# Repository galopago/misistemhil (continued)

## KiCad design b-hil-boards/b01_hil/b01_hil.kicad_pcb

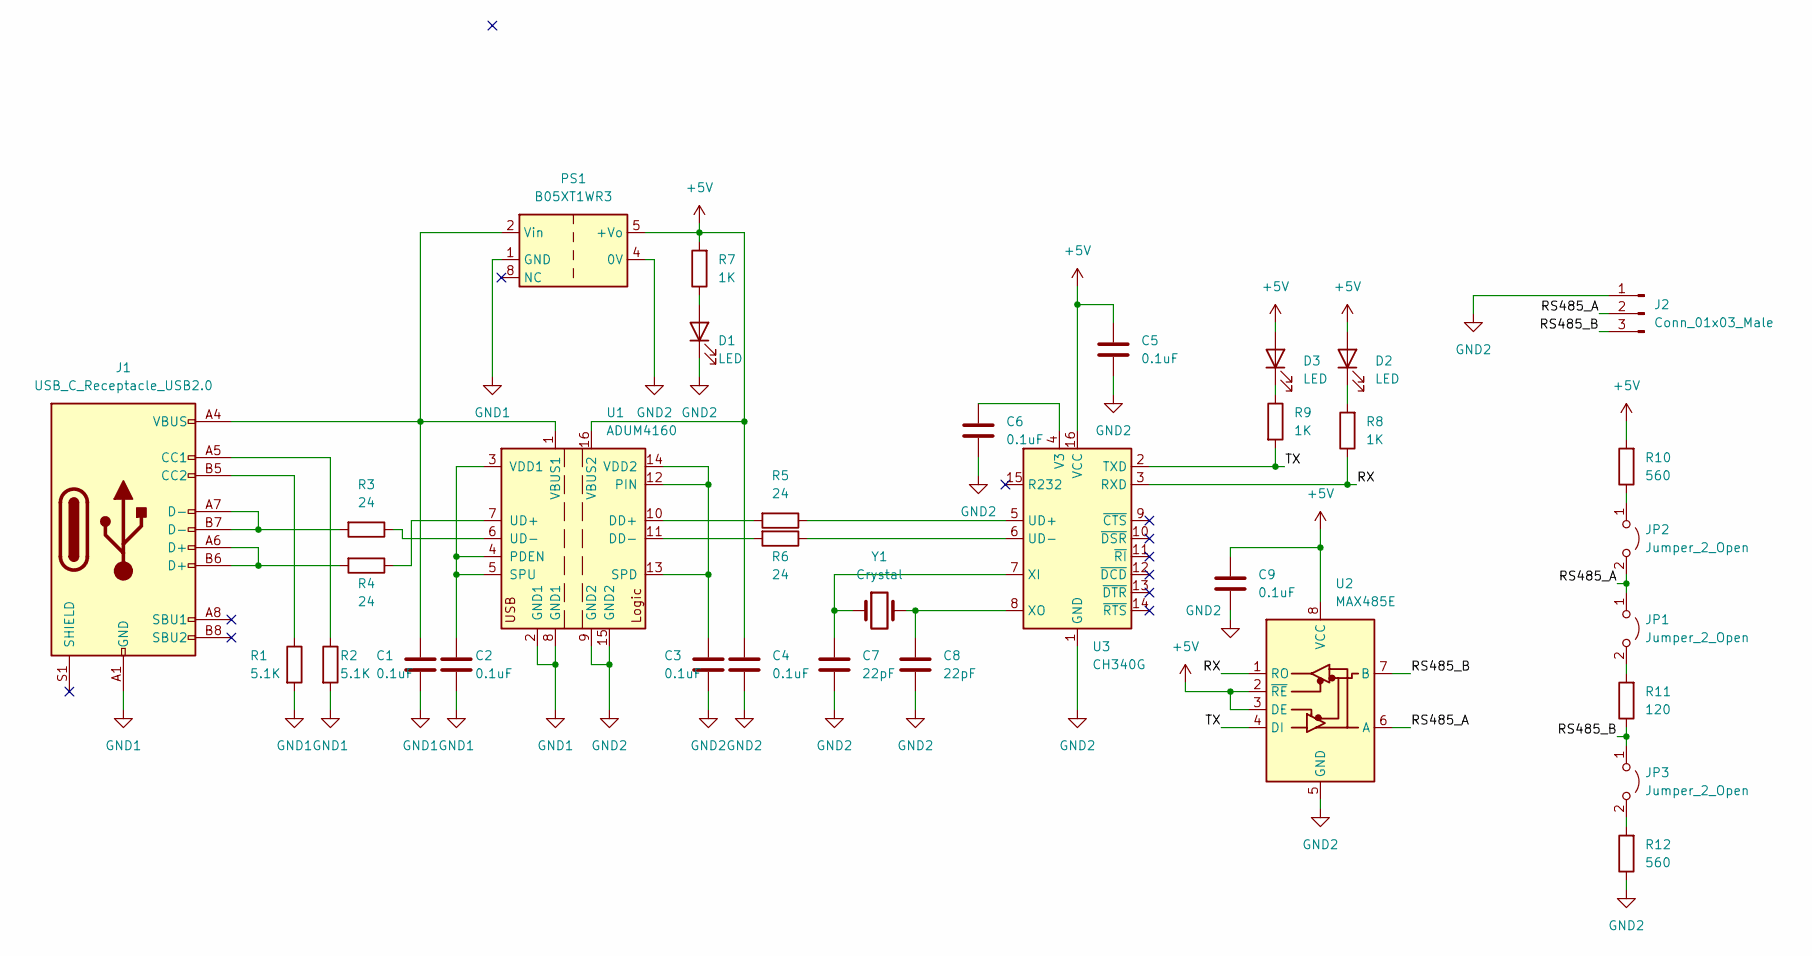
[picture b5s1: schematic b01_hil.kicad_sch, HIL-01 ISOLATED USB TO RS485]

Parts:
C1, C2, C3, C4, C5, C6, C9: 0.1uF; C_0805_2012Metric_Pad1.18x1.45mm_HandSolder
C7, C8: 22pF; C_0805_2012Metric_Pad1.18x1.45mm_HandSolder
D1, D2, D3: LED; D_0805_2012Metric_Pad1.15x1.40mm_HandSolder
J1: USB_C_Receptacle_USB2.0; USB_C_Receptacle_HRO_TYPE-C-31-M-12
J2: Conn_01x03_Male; TerminalBlock_4Ucon_1x03_P3.50mm_Horizontal
JP1, JP2, JP3: Jumper_2_Open; PinHeader_1x02_P2.54mm_Vertical
PS1: B05XT1WR3; Converter_DCDC_Mornsun_B05_XT_1WR3_SMD
R1, R2: 5.1K; R_0805_2012Metric_Pad1.20x1.40mm_HandSolder
R3, R4, R5, R6: 24; R_0805_2012Metric_Pad1.20x1.40mm_HandSolder
R7, R8, R9: 1K; R_0805_2012Metric_Pad1.20x1.40mm_HandSolder
R10, R12: 560; R_0805_2012Metric_Pad1.20x1.40mm_HandSolder
R11: 120; R_0805_2012Metric_Pad1.20x1.40mm_HandSolder
U1: ADUM4160; SOIC-16W_7.5x10.3mm_P1.27mm
U2: MAX485E; SOP-8_3.9x4.9mm_P1.27mm
U3: CH340G; SOIC-16_3.9x9.9mm_P1.27mm
Y1: Crystal; Crystal_SMD_HC49-SD_HandSoldering_Compact

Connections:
+5V: C4.1, C5.1, C9.1, D2.2 (A), D3.2 (A), PS1.5 (+Vo), R7.2, R10.2, U1.16 (VBUS2), U2.2 (~RE), U2.3 (DE), U2.8 (VCC), U3.16 (VCC)
/RS485_A: J2.2, JP1.1 (A), JP2.2 (B), U2.6 (A)
/RS485_B: J2.3, JP3.1 (A), R11.1, U2.7 (B)
/RX: R8.1, U2.1 (RO), U3.3 (RXD)
/TX: R9.2, U2.4 (DI), U3.2 (TXD)
GND1: C1.2, C2.2, J1.A1 (GND), J1.A12 (GND), J1.B1 (GND), J1.B12 (GND), PS1.1 (GND), R1.2, R2.2, U1.2 (GND1), U1.8 (GND1)
GND2: C3.2, C4.2, C5.2, C6.2, C7.2, C8.2, C9.2, D1.1 (K), J2.1, PS1.4 (0V), R12.1, U1.9 (GND2), U1.15 (GND2), U2.5 (GND), U3.1 (GND)
unnamed: C1.1, J1.A4 (VBUS), J1.A9 (VBUS), J1.B4 (VBUS), J1.B9 (VBUS), PS1.2 (Vin), U1.1 (VBUS1)
unnamed: C2.1, U1.3 (VDD1), U1.4 (PDEN), U1.5 (SPU)
unnamed: C3.1, U1.12 (PIN), U1.13 (SPD), U1.14 (VDD2)
unnamed: C6.1, U3.4 (V3)
unnamed: C7.1, U3.7 (XI), Y1.1
unnamed: C8.1, U3.8 (XO), Y1.2
unnamed: D1.2 (A), R7.1
unnamed: D2.1 (K), R8.2
unnamed: D3.1 (K), R9.1
unnamed: J1.A5 (CC1), R2.1
unnamed: J1.A6 (D+), J1.B6 (D+), R4.2
unnamed: J1.A7 (D-), J1.B7 (D-), R3.2
unnamed: J1.B5 (CC2), R1.1
unnamed: JP1.2 (B), R11.2
unnamed: JP2.1 (A), R10.1
unnamed: JP3.2 (B), R12.2
unnamed: R3.1, U1.6 (UD-)
unnamed: R4.1, U1.7 (UD+)
unnamed: R5.1, U3.5 (UD+)
unnamed: R5.2, U1.10 (DD+)
unnamed: R6.1, U3.6 (UD-)
unnamed: R6.2, U1.11 (DD-)

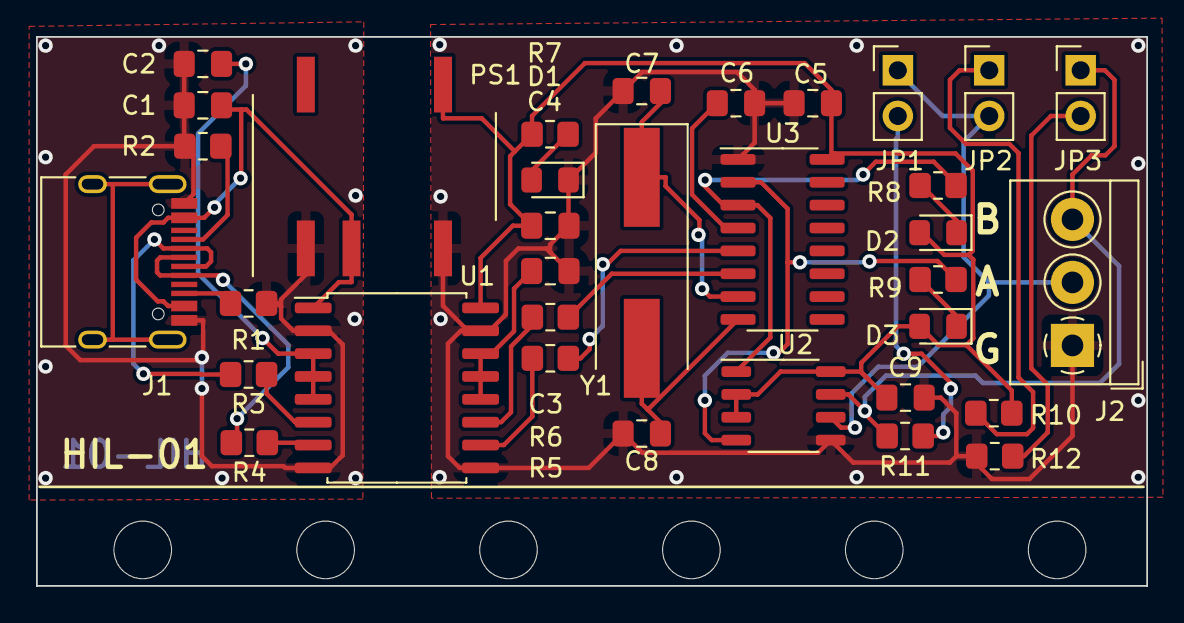
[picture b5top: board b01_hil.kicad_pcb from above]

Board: 2 copper layers, 61.7 x 30.5 mm, 34 parts (0 on the bottom side), 29 nets.

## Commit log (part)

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2024-02-11 hil logo
2024-02-11 started readme
2024-02-11 started readme+
2024-02-11 template readme trimmed
2024-02-13 started 6.35 screw barrier connector footprint
2024-02-19 updated rs485 footprint
2024-02-19 started hil-00 board
2024-02-25 all traces routed
2024-02-25 improved vias on ground planes
2024-02-25 improved vias on ground planes+
2024-02-25 single gerbers
2024-02-25 panel gerbers
2024-02-25 deleted unused files
2024-02-26 panel gerber
2024-08-05 started a00-backplate first test
2024-08-15 started label panels
2024-08-16 fixed name number
2024-10-27 Changed jumper distances to be compatible with 2.54 pin headers
2026-02-18 Start b02 HIL board card
    - Add b02_hil board: schematic, PCB, project and library files
    - Add b02 assets (datasheets, pinout, images) and gerber exports
    - Update b01_hil project files and add b01 backup archives
2026-02-23 B02 card: routing and silkscreen completed
    - PCB layout and silkscreen finished for b02_hil
2026-02-23 B02 card: add gerbers for panelized board
    - Generate panel gerber and drill files in gerber/panel/
2026-02-25 B03: place all board elements (PCB and schematic)
    - Complete component placement for B03 HIL board
    - Add KiCad project, schematic and PCB layout
    - Include symbol/footprint lib tables and fp-info-cache
    - Add project libraries and assets (ESP32-C3, datasheets)
2026-02-25 B03: route all board traces
    - Complete trace routing for B03 HIL board
    - Update PCB layout (b03.kicad_pcb) and schematic (b03.kicad_sch)
    - Add routing session/export files and backups
2026-02-26 B04: complete trace routing for HIL board
    - Add B04 HIL board project with full PCB routing (b04.kicad_pcb, b04.kicad_sch)
    - Include KiCad project, libraries and assets (ESP32-C3, datasheets)
    - Add B03 Gerber panel output (gerber/panel/) for multi-board fabrication
    - Update backups
2026-02-26 B04: add Gerber output for single board
    - Create Gerber files for single-board fabrication (gerber/single/)
    - Include copper, mask, paste, silkscreen, edge cuts and drill files (PTH/NPTH)
    - Add b04-single.zip package for manufacturer
2026-02-26 B04: add Gerber output for panel
    - Create Gerber files for panel fabrication (gerber/panel/)
    - Include copper, mask, paste, silkscreen, edge cuts and drill files
    - Add b04-panel.zip package for multi-board manufacturer
2026-03-19 chore: refresh KiCad backup archives (b02, b03, b04)
    Remove superseded zip snapshots and add current backups under each
    board's *-backups folder.
2026-03-19 fix(b03): correct LED D7 polarity on schematic and PCB
    Fix reversed polarity marking/connection for D7 in b03.kicad_sch and
    b03.kicad_pcb.
2026-03-19 chore(b03): add KiCad backup archive after D7 polarity fix
    Add b03-2026-03-19_183716.zip under b03-backups.
2026-03-19 chore(b02): update panel Gerber outputs
    Refresh layer, drill, and b02-panel.zip exports under gerber/panel/ for
    panelized fabrication.
2026-03-19 chore(b03): update single-board Gerber outputs
    Refresh layer, drill, and b03-single.zip exports under gerber/single/ for
    single-board fabrication.
2026-03-19 chore(b03): update panel Gerber outputs
    Refresh layer, drill, and b03-panel.zip exports under gerber/panel/ for
    panelized fabrication.
2026-05-13 B02: update bottom silkscreen labels
    - Fix B.SilkS VCC/GND text near connector headers on b02.kicad_pcb.
    - Rotate KiCad project backup zip.
    - Remove outdated gerber/single exports.
2026-05-13 B02: update single-board Gerber outputs
    Regenerate gerber/single package (layers, silkscreen, paste, drills, and b02-single.zip) for one-up B02 fabrication.
2026-05-13 B02: update panel Gerber outputs
    Regenerate gerber/panel package (copper, mask, paste, silkscreen, edge cuts, drills, and b02-panel.zip) for panelized B02 fabrication.
2026-05-13 B02: rotate KiCad project backup zip
2026-05-13 Add B05 HIL board KiCad project
    Introduce the new b05_hil design: schematic and PCB sources, project files,
    local symbol/footprint libraries, datasheet assets, FreeRouting artifacts
    (b02.dsn/rules/ses), KiCad automatic backups, and single/panel Gerber outputs.
2026-05-13 d00_hil_faceplate: add initial KiCad project files
    Create the d-faceplates/d00_hil_faceplate tree with starter schematic, PCB, project and library files, fp-info-cache, and KiCad automatic backups.
2026-05-13 d01_hil_faceplate: add initial KiCad project files
    Create the d-faceplates/d01_hil_faceplate tree with starter schematic, PCB, project and library files, fp-info-cache, and KiCad automatic backups.
2026-05-13 d01_hil_faceplate: add single-board Gerber outputs
    Export gerber/single (copper, mask, paste, silkscreen, edge cuts, drills, and d01-hil-faceplate-single.zip), refresh PCB and fp-info-cache, and rotate KiCad automatic backup.
2026-05-13 d01_hil_faceplate: add panel Gerber outputs
    Add gerber/panel exports (copper, mask, paste, silkscreen, edge cuts, drills, and d01-hil-faceplate-panel.zip) for panelized fabrication; rotate KiCad automatic backup.
2026-05-13 d-faceplates: regenerate Gerber outputs after fabrication issues
    Previous d01_hil_faceplate panel exports were incorrect; replace the full
    gerber/panel set and packaged zip with corrected manufacturing files.
    Rotate KiCad automatic backups for d00 and d01 faceplate projects.
2026-05-15 B00: add latest KiCad automatic backup
    Track new b00_hil-backups snapshot archive.
2026-05-15 d01_hil_faceplate: refresh KiCad automatic backups
    Remove two older d01_hil_faceplate-backups zips and add the latest project snapshots.
2026-05-15 d00_hil_faceplate: add single-board Gerber outputs
    Export gerber/single (copper, mask, paste, silkscreen, edge cuts, drills, and d00-hil-faceplate-single.zip), refresh PCB, and rotate KiCad automatic backups.
2026-05-16 B06: add single-board Gerber outputs
    Export gerber/single (copper, mask, paste, silkscreen, edge cuts, drills, and b06-single.zip) for one-up fabrication; refresh PCB, schematic, and project layout; rotate KiCad automatic backups.
2026-05-16 B06: add panel Gerber outputs
    Add gerber/panel exports (copper, mask, paste, silkscreen, edge cuts, drills, and b06-panel.zip) for panelized PCB fabrication; rotate KiCad automatic backup.
2026-05-22 B03: add tri-state buffer and re-route PCB
    Add 74HCT541 tri-state buffer to the schematic and re-route b03.kicad_pcb
    to integrate the new device. Update project settings, replace FreeRouting
    exchange files (b03.dsn, b03.rules, b03.ses; remove legacy b02.*), and
    rotate KiCad automatic backup archives.
2026-05-22 B03: add panel Gerber outputs
    Add gerber/panel exports (copper, mask, paste, silkscreen, edge cuts, drills, and b03-panel.zip) for panelized PCB fabrication.
2026-05-25 B02: add tri-state buffer and re-route PCB
    Add 74HCT541 tri-state buffer to the schematic and re-route b02.kicad_pcb
    to integrate the new device. Update project layout, refresh FreeRouting
    exchange files (b02.dsn, b02.rules, b02.ses), and rotate KiCad automatic
    backup archives.
2026-05-25 B02: add single-board Gerber outputs
    Export gerber/single (copper, mask, paste, silkscreen, edge cuts, drills, and b02-single.zip) for one-up fabrication; refresh PCB and rotate KiCad automatic backup.
2026-06-20 refactor(b06): move KiCad project into pcb/ subdirectory
2026-06-20 chore: update KiCad backups across boards and faceplates
    Replace outdated backup archives with current snapshots for b02, b03, b04, b05, and d00.
2026-06-20 docs(firmware): define OLED display architecture milestone
    Record the initial OLED display interface contract and handoff so implementation can proceed without redefining rendering, layout, or validation boundaries.
2026-06-20 Record b06_hil firmware architecture milestone and I2C foundation.
    Document ESP32-C3 board connections, portable shared I2C bus design, phased
    concurrency, agent role boundaries, and validation criteria. Add ESP-IDF
    firmware with display stack, i2c_bus phases 1-2, and architect/implementer/
    tester handoffs for this checkpoint.
2026-06-22 docs(firmware): clarify instruction-driven QR and unified refresh.
    QR appears only on explicit draw instructions with a URL; the display does not
    wait for IP. QR payload updates use the same refresh path as any other display
    content change.
2026-06-22 docs(firmware): define v1 printable ASCII-only display text policy.
    Document that product strings use ASCII only with no accents or other scripts;
    unsupported characters sanitize to ? at render time.
2026-06-22 docs(firmware): specify root-only HTTP QR URLs and no HTTPS in v1.
    QR payloads are http://IPv4 with implicit / only; subpath redirects belong to
    another entity. HTTPS is excluded as unlikely for small-MCU local setup.
2026-06-22 docs(firmware): exclude display power management for occasional-use v1.
    Document that OLED sleep, dimming, and panel power-off are out of scope because
    the product is not intended for continuous 24/7 operation.
2026-06-22 docs(firmware): define app_core display delivery contract for v1.
    Document centralized orchestration: producers notify app_core via callback or
    esp_event; only app_core calls display_controller APIs directly with no polling
    or application-level display queue.
2026-06-22 docs(firmware): decouple display from network and pin callback transport.
    Treat QR and text as the same display instruction path through app_core;
    remove WiFi/network coupling from display architecture and select callback
    (not esp_event) as the v1 notification mechanism.
2026-06-22 docs(firmware): add architect hard stop and visual demo protocol.
    Document non-negotiable architect boundaries (no code, no builds), override
    hierarchy over mixed plans, OLED boot demo handoff rules, and role templates.
2026-06-22 docs(firmware): add immutable architect mission pillar.
    Define task completion as documentation and handoff only; pillar outranks
    plans, todos, and conflicting prompts while role is architect.
2026-06-23 docs(firmware): align display architecture with implementation snapshot.
    Pin the implemented app_core display facade, QR setup path, setup_url and Nayuki
    component layout, static QR encoder behavior, and visual demo contract so future
    LLM implementers reproduce the same v1 structure.
2026-06-24 docs(firmware): add as-built WiFi connect cycle v2 reference
    Capture operator-validated connect cycle and LED behavior in an
    implementation-ready reference, align architecture specs and handoffs,
    and mark boot lock/HOLD RESET paths as obsolete for faithful replay.
2026-06-24 feat(b06_hil): implement unified WiFi connect cycle and error LED v2
    Add infinite boot/runtime reconnect rounds with alert-phase LED feedback,
    remove saved boot lock and HOLD RESET paths, and wire GPIO8 error_led
    through app_core link_status mapping validated by operator testing.
